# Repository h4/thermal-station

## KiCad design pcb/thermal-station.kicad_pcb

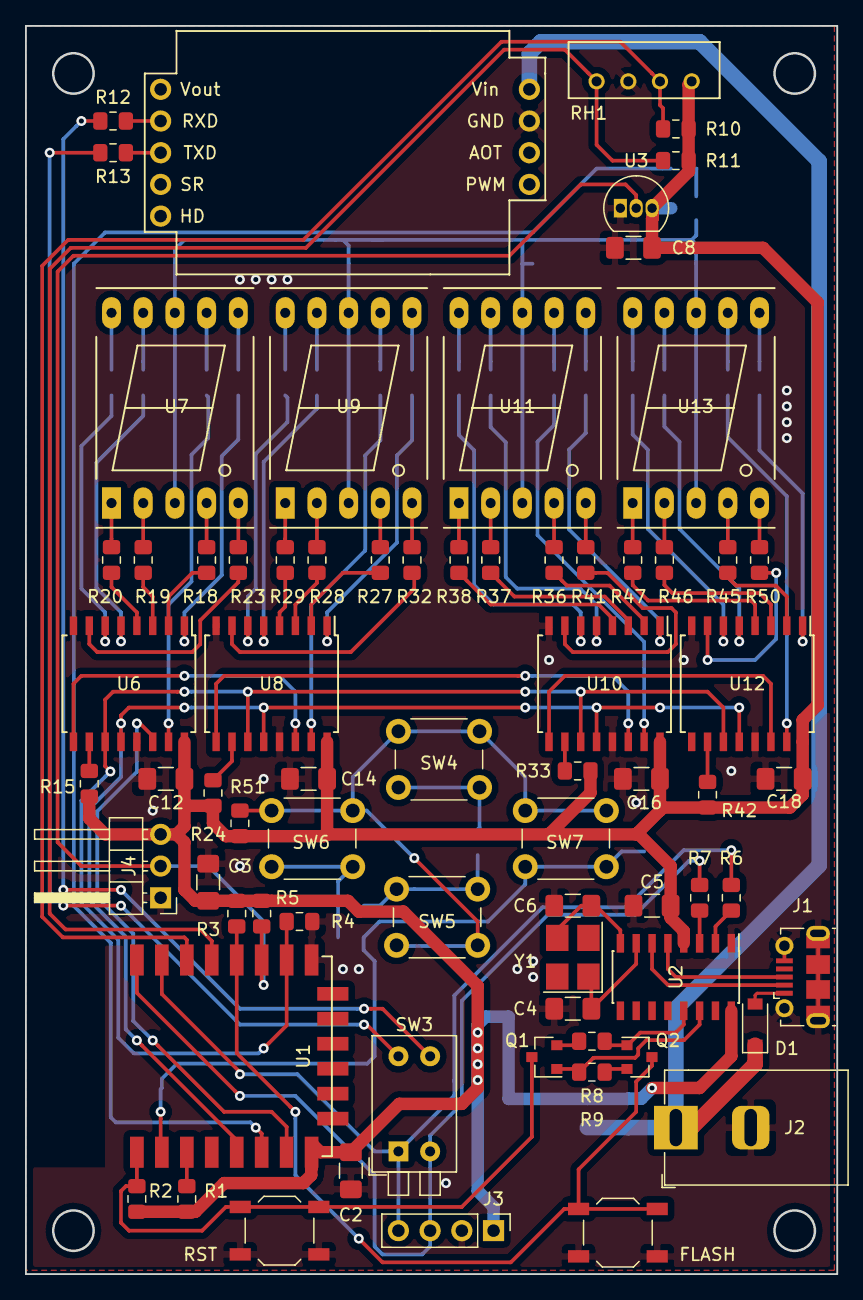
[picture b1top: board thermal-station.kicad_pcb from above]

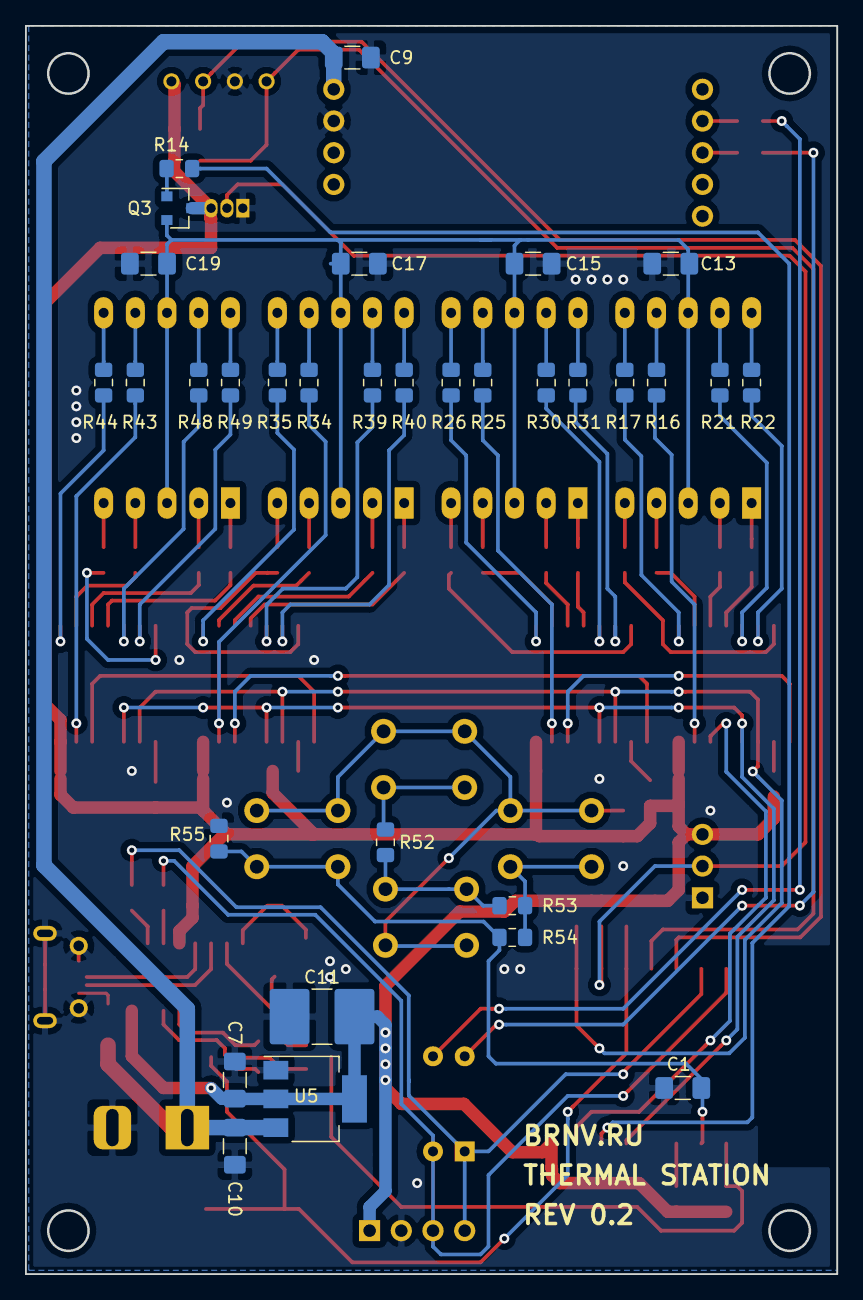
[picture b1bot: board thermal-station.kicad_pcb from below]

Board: 2 copper layers, 65.0 x 100.0 mm, 104 parts (32 on the bottom side), 108 nets.

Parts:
C1, C2, C3, C8, C9, C12, C13, C14, C15, C16, C17, C18, C19: 0.1uF; C_1206_3216Metric_Pad1.42x1.75mm_HandSolder
C4, C6: 22pF; C_1206_3216Metric_Pad1.42x1.75mm_HandSolder
C5, C7, C10: 10uF; C_1206_3216Metric_Pad1.42x1.75mm_HandSolder
C11: 100uF; C_2816_7142Metric_Pad3.20x4.45mm_HandSolder
D1: B240A-E3; D_SOD-123
FLASH: FLASH; SW_SPST_TL3342
J1: USB; USB_Micro-B_Molex-105017-0001
J2: Jack-DC; BarrelJack_Horizontal_DS_201
J3: Conn_01x04_Male; PinHeader_1x04_P2.54mm_Vertical
J4: Conn_01x03; PinHeader_1x03_P2.54mm_Horizontal
Q1, Q2: S8050; SOT-23
Q3: IRLML2502; SOT-23
R1, R2, R3, R4, R5, R8, R9: 10K; R_0805_2012Metric_Pad1.15x1.40mm_HandSolder
R6, R7: 470; R_0805_2012Metric_Pad1.15x1.40mm_HandSolder
R10, R11: 2K2; R_0805_2012Metric_Pad1.15x1.40mm_HandSolder
R12, R13: 4K7; R_0805_2012Metric_Pad1.15x1.40mm_HandSolder
R14, R15, R24, R33, R42: 1K; R_0805_2012Metric_Pad1.15x1.40mm_HandSolder
R16, R17, R18, R19, R20, R21, R22, R23, R25, R26, R27, R28, R29, R30, R31, R32, R34, R35, R36, R37, R38, R39, R40, R41, R43, R44, R45, R46, R47, R48, R49, R50: 160; R_0805_2012Metric_Pad1.15x1.40mm_HandSolder
R51, R52, R53, R54, R55: 56K; R_0805_2012Metric_Pad1.15x1.40mm_HandSolder
RH1: AM2320
RST: RESET; SW_SPST_TL3342
SW3: SW_DIP_x02; SW_DIP_SPSTx02_Piano_10.8x6.64mm_W7.62mm_P2.54mm
SW4: BRIGHT UP; SW_PUSH_6mm_H8.5mm
SW5: BRIGHT DOWN; SW_PUSH_6mm_H8.5mm
SW6: NEXT; SW_PUSH_6mm_H8.5mm
SW7: PREV; SW_PUSH_6mm_H8.5mm
U1: ESP-12E; ESP-12E_SMD
U2: CH340G; SOIC-16_3.9x9.9mm_P1.27mm
U3: DS18B20; TO-92_Inline
U4: MH-Z19
U5: LM1117-3.3; SOT-223-3_TabPin2
U6, U8, U10, U12: 74HC595; SOIC-16W_7.5x10.3mm_P1.27mm
U7, U9, U11, U13: KCSA02-105; 7SegmentLED_LTS6760_LTS6780
Y1: HC-49; Crystal_SMD_SeikoEpson_FA238V-4Pin_3.2x2.5mm_HandSoldering

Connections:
1WIRE: J4.2, R5.1, U1.11, U3.2
+3V3: C2.1, C3.1, C5.1, C7.1, C8.1, C11.1, C12.1, C14.1, C16.1, C18.1, J3.1, J4.3, Q3.3, R1.2, R2.2, R3.2, R5.2, R10.1, R11.1, R15.1, R24.1, R33.1, R42.1, R51.2, RH1.1, U1.8, U2.4, U2.16, U3.3, U5.2, U6.16, U8.16, U10.16, U12.16
+5V: C9.1, C10.1, D1.1, J2.1, U4.6, U5.3
/DISPLAY/LED_1/QA: R16.2, U6.15
/DISPLAY/LED_1/QB: R17.2, U6.1
/DISPLAY/LED_1/QC: R18.2, U6.2
/DISPLAY/LED_1/QD: R19.2, U6.3
/DISPLAY/LED_1/QE: R20.2, U6.4
/DISPLAY/LED_1/QF: R21.2, U6.5
/DISPLAY/LED_1/QG: R22.2, U6.6
/DISPLAY/LED_1/QH: R23.2, U6.7
/DISPLAY/LED_2/DATA_IN: U6.9, U8.14
/DISPLAY/LED_2/QA: R25.2, U8.15
/DISPLAY/LED_2/QB: R26.2, U8.1
/DISPLAY/LED_2/QC: R27.2, U8.2
/DISPLAY/LED_2/QD: R28.2, U8.3
/DISPLAY/LED_2/QE: R29.2, U8.4
/DISPLAY/LED_2/QF: R30.2, U8.5
/DISPLAY/LED_2/QG: R31.2, U8.6
/DISPLAY/LED_2/QH: R32.2, U8.7
/DISPLAY/LED_3/DATA_IN: U8.9, U10.14
/DISPLAY/LED_3/QA: R34.2, U10.15
/DISPLAY/LED_3/QB: R35.2, U10.1
/DISPLAY/LED_3/QC: R36.2, U10.2
/DISPLAY/LED_3/QD: R37.2, U10.3
/DISPLAY/LED_3/QE: R38.2, U10.4
/DISPLAY/LED_3/QF: R39.2, U10.5
/DISPLAY/LED_3/QG: R40.2, U10.6
/DISPLAY/LED_3/QH: R41.2, U10.7
/DISPLAY/LED_4/DATA_IN: U10.9, U12.14
/DISPLAY/LED_4/QA: R43.2, U12.15
/DISPLAY/LED_4/QB: R44.2, U12.1
/DISPLAY/LED_4/QC: R45.2, U12.2
/DISPLAY/LED_4/QD: R46.2, U12.3
/DISPLAY/LED_4/QE: R47.2, U12.4
/DISPLAY/LED_4/QF: R48.2, U12.5
/DISPLAY/LED_4/QG: R49.2, U12.6
/DISPLAY/LED_4/QH: R50.2, U12.7
ADC: C1.1, R54.1, R55.2, SW7.2, U1.2
Clock: U1.5, U6.12, U8.12, U10.12, U12.12
Earth: C1.2, C2.2, C3.2, C4.2, C5.2, C6.2, C7.2, C8.2, C9.2, C10.2, C11.2, C12.2, C13.2, C14.2, C15.2, C16.2, C17.2, C18.2, C19.2, FLASH.2, J1.5, J1.6, J2.2, J3.2, J4.1, R4.1, R55.1, RH1.3, RST.1, U1.9, U2.1, U3.1, U4.7, U5.1, U6.8, U6.13, U8.8, U8.13, U10.8, U10.13, U12.8, U12.13
GPIO0: FLASH.1, Q2.3, R3.1, U1.12
LED_CA: C13.1, C15.1, C17.1, C19.1, Q3.2, U7.3, U7.8, U9.3, U9.8, U11.3, U11.8, U13.3, U13.8
MOSI: U1.7, U6.14
unnamed: C4.1, U2.7, Y1.1
unnamed: C6.1, U2.8, Y1.3
unnamed: D1.2, J1.1
unnamed: J1.2, U2.6
unnamed: J1.3, U2.5
unnamed: Q1.1, R9.2, U2.14
unnamed: Q1.2, R8.1
unnamed: Q2.1, R8.2, U2.13
unnamed: Q2.2, R9.1
unnamed: Q3.1, R14.2
unnamed: R1.1, U1.3
unnamed: R6.2, U2.2
unnamed: R7.2, U2.3
unnamed: R12.1, SW3.3
unnamed: R12.2, U4.2
unnamed: R13.1, SW3.4
unnamed: R13.2, U4.3
unnamed: R15.2, U6.10
unnamed: R16.1, U7.7
unnamed: R17.1, U7.6
unnamed: R18.1, U7.4
unnamed: R19.1, U7.2
unnamed: R20.1, U7.1
unnamed: R21.1, U7.9
unnamed: R22.1, U7.10
unnamed: R23.1, U7.5
unnamed: R24.2, U8.10
unnamed: R25.1, U9.7
unnamed: R26.1, U9.6
unnamed: R27.1, U9.4
unnamed: R28.1, U9.2
unnamed: R29.1, U9.1
unnamed: R30.1, U9.9
unnamed: R31.1, U9.10
unnamed: R32.1, U9.5
unnamed: R33.2, U10.10
unnamed: R34.1, U11.7
unnamed: R35.1, U11.6
unnamed: R36.1, U11.4
unnamed: R37.1, U11.2
unnamed: R38.1, U11.1
unnamed: R39.1, U11.9
unnamed: R40.1, U11.10
unnamed: R41.1, U11.5
unnamed: R42.2, U12.10
unnamed: R43.1, U13.7
unnamed: R44.1, U13.6
unnamed: R45.1, U13.4
unnamed: R46.1, U13.2
unnamed: R47.1, U13.1
unnamed: R48.1, U13.9
unnamed: R49.1, U13.10
unnamed: R50.1, U13.5
unnamed: R51.1, SW4.1, SW5.1, SW6.1, SW7.1
unnamed: R52.1, R53.2, SW5.2
unnamed: R52.2, SW4.2
unnamed: R53.1, R54.2, SW6.2
PWM: R14.1, U1.6
RST: Q1.3, R2.1, RST.2, U1.1
RXD: J3.4, R6.1, SW3.1, U1.15
SCL: R11.2, RH1.4, U1.13
SDA: R10.2, RH1.2, U1.14
SS: R4.2, U1.10, U6.11, U8.11, U10.11, U12.11
TXD: J3.3, R7.1, SW3.2, U1.16

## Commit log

2019-03-25 Redesign PCB
